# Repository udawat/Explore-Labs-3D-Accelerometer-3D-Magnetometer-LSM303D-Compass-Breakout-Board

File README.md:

# Explore Labs 3D Accelerometer + 3D Magnetometer LSM303D Compass Breakout Board
## Overview

[Explore Labs 3D Accelerometer + 3D Magnetometer LSM303D Compass Breakout Board](http://www.explorelabs.com/explore-labs-3d-accelerometer-3d-magnetometer-lsm303d-compass-breakout-board-5v-ready-with-voltage-regulator "Explore Labs 3D Accelerometer + 3D Magnetometer LSM303D Compass Breakout Board") is based on the ST LSM303D sensor, a 3D digital linear acceleration sensor and a 3D digital magnetic sensor that is ideal for making a tilt-compensated compass.

The LSM303D includes an I2C serial bus interface that supports standard and fast mode (100 kHz and 400 kHz) and SPI serial standard interface. The system can be configured to generate an interrupt signal for free-fall, motion detection and magnetic field detection. Thresholds and timing of interrupt generators are programmable by the end user. Magnetic and accelerometer blocks can be enabled or put into power-down mode separately.

The carrier board includes a low-dropout linear voltage regulator that provides the 3.3 V required by the LSM303D, which allows the sensor to be powered from 2.5 V to 5.5 V. The regulator output is available on the 3Vo pin which can supply approx. 150 mA to external devices.

The breakout board also includes a circuit that shifts the two I2C lines or all four SPI lines (clock, data-in/out and chip select) to the same logic voltage level as the supplied VIN, making it simple to interface the board with 5V systems; and the board’s 0.1″ pin spacing makes it easy to use with standard solderless breadboards and 0.1″ perfboards. The board ships fully populated with its SMD components, including the LSM303D, as shown in the product picture.

## Features of Explore Labs 3D Accelerometer + 3D Magnetometer LSM303D Compass Breakout Board:
* Wide supply voltage - 2.5V to 5V
* Level shifted IO lines for easy interfacing to high voltage boards like Arduino Uno, Mega, Leonardo, etc.
* All pins of the LSM303D sensor are available like I2C and SPI communication interfaces as well as INT1 and INT2 Interrupt pins
* Layout takes care of keeping the area below the sensor free from any active current carrying trace or a power or ground plane
* Capacitors with low ESR characteristics are used for decoupling on both VDD and VDDIO power inputs
* Open Source Hardware
* Designed, Assembled and Made in India

## Features of LSM303D Sensor IC:
* 3 magnetic field channels and 3 acceleration channels
* &plusmn;2/&plusmn;4/&plusmn;8/&plusmn;12 gauss magnetic full scale
* &plusmn;2/&plusmn;4/&plusmn;6/&plusmn;8/&plusmn;16 g linear acceleration full scale
* 16-bit data output
* SPI / I2C serial interfaces
* Power-down mode / low-power mode
* Extended operating temperature range (from -40 °C to 85 °C)
* Programmable interrupt generators for free-fall, motion detection and magnetic field detection
* Embedded temperature sensor
* Embedded FIFO

## Specifications:
* Input Voltage: 2.5V to 5V
* 5V Ready IOs: Level shifted IO lines for easy interfacing to incompatible voltage boards
* Digital Output: Inter Integrated Circuit (I2C/IIC) or Serial Peripheral Interface (SPI)
* Regulator Pin - Provides 3.3V Out at 150mA (when 3.6V < VIN < 5V) else provides voltage ~equal to VIN
* Dimensions: 20.4 mm x 20 mm
* Weight: 3 grams

## Applications:
* Tilt-compensated compasses
* Map rotation
* Position detection
* Motion-activated functions
* Free-fall detection
* Click/double-click recognition
* Pedometers
* Intelligent power saving for handheld devices
* Display orientation
* Gaming and virtual reality input devices
* Impact recognition and logging
* Vibration monitoring and compensation

## Output Format:
Values are expressed in 16-bits as two’s complement for each axis. As shown in the example codes below, knowing the sensitivites of the device, one can easily find out the acceleration value in g (acceleration due to gravity) and magnetic field intensity in gauss. These readings may be used separately or together to create a tilt-compensated compass or other complex orientation calculations for Inertial Measurement Units (IMU).

## Pinout Table for Explore Labs 3D Accelerometer + 3D Magnetometer LSM303D Compass Breakout
|Pin|5V Safe?   |Function|
|---|-----------|--------|
|VIN|Yes|**Input Voltage** Pin: 2.5V to 5.0V (depending on Master device being used as mentioned in later connection sections and tables below)|
|3Vo|Not Applicable|This is the output pin of the onboard 3.3V Voltage Regulator. It provides a clean and regulated 3.3V output to the sensor IC. It can also be used by the user to provide power to external devices or sensors. Maximum current that can be sourced easily would be approximately 125mA to 150mA after leaving some room for the on board sensor IC|
|GND|Not Applicable|Ground Connection. Connect this pin to the master device's ground pin or to any externally powered devices from onboard regulator|
|SDI/SDA|Yes. Bidirectional MOSFET with 4K7 pull-ups|This pin has dual functions - **Serial Data Input** (for SPI) or **Serial Data** (for I2C). In case of SPI, it can also be called as Master Out Slave In (MOSI)|
|SCK/SCL|Yes. Bidirectional MOSFET with 4K7 pull-ups|This pin is the **Serial Clock** input pin. It is common for both SPI and I2C interfaces|
|SDO/ADR|Yes. Only a 4K7 pull-up resistor needed as this is an output pin|This pin has dual functions - **Serial Data Output** (for SPI) or **Address Select** (for I2C). Also called as SA0. In case of SPI, it can also be called as Master In Slave Out (MOSI). In case of I2C, this pin may be pulled LOW or grounded for selecting an alternate address to avoid address conflicts with similar I2C devices. The change will have to be updated in code as well. Leave unconnected if no change in address required for I2C|
|CS|Yes. Bidirectional MOSFET with 4K7 pull-ups|**Chip Select** or Slave Select pin. By default, it is pulled HIGH using an onboard 4K7 pull-up resistor. This sets the default mode of communication for the sensor IC as I2C. For SPI, this pin acts as the chip select pin to communicate with an SPI master device. Leave unconnected when using I2C|
|INT1|No|Interrupt output pin. The LSM303D interrupt signal can be configured in a very flexible way allowing to recognize independent magnetic field detections of the X, Y and Z-axis. Or, independently recognize inertial events like an interrupt is generated when orientation moves from an unknown zone to a known zone. Single click and double clicks on any individual axis can easily be detected using any interrupt pin. FIFO Programmable threshold level, FIFO_empty or FIFO_Full events can be enabled to generate dedicated interrupts on the INT 1 or INT 2 pin. Also, An interrupt can be generated when the magnetic field value exceeds the user-defined threshold. The threshold and the timing of the two interrupt pins (INT 1 and INT 2) can be completely programmed by the user through the I2C/SPI interfaces. A detailed explanation is available in the ST LSM303D datasheet|
|INT2|No|Second Interrupt output pin. This pin acts as an additional interrupt pin for the LSM303D. It has the same functionality as of the INT1 pin. For more details, see INT1|
|GND|Not Applicable|Second Ground connection. Optionally, connect this pin to the master device's ground pin or to any externally powered devices from onboard regulator|

## Connections

The carrier board supports both I2C as well as SPI method of communication with a host microcontroller. The communication mode is selected by pulling the CS pin HIGH or LOW. By default, the CS pin is pulled HIGH through a 4.7 kΩ resistor on the board. This makes I2C communication the default method to talk to this carrier board.

**I2C Communication**: By default, I2C communication is implemented. The Explore Labs 3D Accelerometer + 3D Magnetometer LSM303D Compass Breakout Board can be configured and its angular velocity readings can be queried through the I2C bus. Level shifters on the I2C clock (SCL) and data (SDA) lines enable I2C communication with microcontrollers operating at the same voltage as VIN (2.5V to 5V). A detailed explanation of the I2C interface on the LSM303D can be found in its [datasheet][1] and more detailed information about I2C Protocol in general can be found in [NXP’s I2C-bus specification manual][2].

**I2C Address**: In I2C mode, the device’s 7-bit slave address has its least significant bit (LSb) determined by the voltage on the SDO/ADR pin. The carrier board pulls SDO/ADR HIGH through a 4.7 kΩ resistor, making the LSb 1 and setting the slave address to 0011101b (0x1D). This is the default device address in I2C mode. If SDO/ADR pin is connected to ground, LSb value is ‘0’ which changes the device address to 0011110b (0x1E). This solution permits the connection and addressing of two different accelerometers to the same I2C lines.

**Arduino Uno with I2C Interface**
* Sensor VIN - Arduino Uno 5V
* Sensor GND - Arduino Uno GND
* Sensor SDI/SDA - Arduino Uno Analog Input Pin A4 or SDA
* Sensor SCK/SCL - Arduino Uno Analog Input Pin A5 or SCL

**Raspberry Pi (all models) with I2C Interface**
* Sensor VIN - Raspberry Pi 3.3V on Pin 1 or 17
* Sensor GND - Raspberry Pi GND
* Sensor SDI/SDA - Raspberry Pi SDA1 (I2C) on Pin 3 or GPIO2
* Sensor SCK/SCL - Raspberry Pi SCL1 (I2C) on Pin 5 or GPIO3

**BeagleBone Black with I2C Interface**
* Sensor VIN - BeagleBone Black 3.3V
* Sensor GND - BeagleBone Black GND
* Sensor SDI/SDA - BeagleBone Black I2C2_SDA (Pin 20) on Header P9
* Sensor SCK/SCL - BeagleBone Black I2C2_SCL (Pin 19) on Header P9

## Connecting Explore Labs 3D Accelerometer + 3D Magnetometer LSM303D Compass Breakout Board using I2C (Inter Integrated Circuit) Interface
|L3GD20H|Arduino Uno|Arduino Mega|Arduino Leonardo|Arduino Due|Genuino Zero|Genuino 101|Arduino MKR1000|Raspberry Pi|BeagleBone Black|
|---|---|---|---|---|---|---|---|---|---|
|**VIN**|5V|5V|5V|3.3V|3.3V|VCC (3.3V)|3.3V|3.3V|3.3V|
|**GND**|GND|GND|GND|GND|GND|GND|GND|GND|GND|
|**SDI/SDA**|A4 or SDA|Pin 20 (SDA)|Pin 2 (SDA)|Pin 20 (SDA)|SDA|SDA|Pin 12 (SDA)|Pin 3 (SDA1) or GPIO2|Pin 20 (I2C2_SDA)|
|**SCK/SCL**|A5 or SCL|Pin 21 (SCL)|Pin 3 (SCL)|Pin 21 (SCL)|SCL|SCL|Pin 11 (SCL)|Pin 5 (SCL1) or GPIO3|Pin 19 (I2C2_SCL)|

## SPI Communication:
To use the LSM303D in SPI mode, CS pin must be driven low (connected to GND). A minimum of four logic connections are used viz., SDI, SCK, SDO and CS. These should be connected to an SPI bus operating at the same logic level as VIN. The SPI interface operates in 4-wire mode by default, with SDI and SDO on separate pins. In the default 4-wire mode, the sensor transmits data to the SPI master on a dedicated data out (SDO) line. If the SPI interface is configured to use 3-wire mode instead, the SDI line doubles as SDO and is driven by the LSM303D when it transmits data to the master. A detailed explanation of the SPI interface on the LSM303D can be found in its [datasheet][1].

**Arduino Uno with Serial Peripheral Interface (SPI)**
* Sensor VIN - Arduino Uno 5V
* Sensor GND - Arduino Uno GND
* Sensor SDI/SDA - Arduino Uno Digital Pin 11 or MOSI (Master Out Slave In)
* Sensor SCK/SCL - Arduino Uno Digital Pin 13 or SCK (Serial Clock)
* Sensor SDO/ADR - Arduino Uno Digital Pin 12 or MISO (Master In Slave Out)
* Sensor CS - Arduino Uno Digital Pin 10 or SS (Slave Select or Chip Select)

**Raspberry Pi (all models) with Serial Peripheral Interface (SPI)**
* Sensor VIN - Raspberry Pi 3.3V on Pin 1 or 17
* Sensor GND - Raspberry Pi GND
* Sensor SDI/SDA - Raspberry Pi `MOSI` (SPI) on Pin 19 or GPIO10
* Sensor SCK/SCL - Raspberry Pi `SCLK` (SPI) on Pin 23 or GPIO11
* Sensor SDO/ADR - Raspberry Pi `MISO` (SPI) on Pin 21 or GPIO9
* Sensor CS - Raspberry Pi `CE0_N` (SPI) on Pin 24 or GPIO8

**BeagleBone Black with Serial Peripheral Interface (SPI)**
* Sensor VIN - BeagleBone Black 3.3V
* Sensor GND - BeagleBone Black GND
* Sensor SDI/SDA - BeagleBone Black `SPI0_D0` (Pin 21) on Header P9
* Sensor SCK/SCL - BeagleBone Black `SPI0_SCLK` (Pin 22) on Header P9
* Sensor SDO/ADR - BeagleBone Black `SPI0_D1` (Pin 18) on Header P9
* Sensor CS - BeagleBone Black `SPI0_CS0` (Pin 17) on Header P9

## Connecting Explore Labs 3D Accelerometer + 3D Magnetometer LSM303D Compass Breakout Board using Serial Peripheral Interface (SPI)
|L3GD20H|Arduino Uno|Arduino Mega|Arduino Leonardo|Arduino Due|Genuino Zero|Genuino 101|Arduino MKR1000|Raspberry Pi|BeagleBone Black|
|---|---|---|---|---|---|---|---|---|---|
|**VIN**|5V|5V|5V|3.3V|3.3V|VCC (3.3V)|3.3V|3.3V|3.3V|
|**GND**|GND|GND|GND|GND|GND|GND|GND|GND|GND|
|**SDI/SDA**|Pin 11 or MOSI|Pin 51|Pin 4 (ICSP)|Pin 4 (ICSP)|Pin 4 (ICSP)|Pin 11 (MOSI)|Pin 8 (MOSI)|Pin 19 (`MOSI`) or GPIO10|Pin 21 (`SPI0_D0`)|
|**SCK/SCL**|Pin 13 or SCK|Pin 52|Pin 3 (ICSP)|Pin 3 (ICSP)|Pin 3 (ICSP)|Pin 13|Pin 9|Pin 23 (`SCLK`) or GPIO11|Pin 22 (`SPI0_SCLK`)|
|**SDO/ADR**|Pin 12 or MISO|Pin 50|Pin 1 (ICSP)|Pin 1 (ICSP)|Pin 1 (ICSP)|Pin 12 (MISO)|Pin 10 (MISO)|Pin 21 (`MISO`) or GPIO9|Pin 18 (`SPI0_D1`)|
|**CS**|Pin 10 or SS|Pin 53|Any IO|Any IO|Any IO|Pin 10|Any IO|Pin 24 (`CE0_N`) or GPIO8|Pin 17 (`SPI0_CS0`)|

## Resources:
[1]: www.st.com/resource/en/datasheet/lsm303d.pdf
[2]: http://www.nxp.com/documents/user_manual/UM10204.pdf
[Datasheet ST LSM303D: e-compass: 3D accelerometer and 3D magnetometer module](www.st.com/resource/en/datasheet/lsm303d.pdf "Datasheet ST LSM303D: e-compass: 3D accelerometer and 3D magnetometer module")

## Code:
Sample code is provided for interfacing the Explore Labs 3D Accelerometer + 3D Magnetometer LSM303D Compass Breakout Board to an Arduino Uno. After choosing the communication method (I2C or SPI), following code examples can be used to test the sensor.

**Using SPI**:
```c
/*
 * Interface Code for Explore Labs 3D Accelerometer + 3D Magnetometer
 * LSM303D Compass Breakout Board and Arduino Uno. This code assumes
 * selected communication method is Serial Peripheral Interface (SPI)
 * and hardware connections are made as follows:
 * 
 * Sensor VIN - Arduino Uno 5V or 3.3V
 * Sensor GND - Arduino Uno GND
 * Sensor SDI/SDA - Arduino Uno Digital Pin 11 or MOSI (Master Out Slave In)
 * Sensor SCK/SCL - Arduino Uno Digital Pin 13 or SCK (Serial Clock)
 * Sensor SDO/ADR - Arduino Uno Digital Pin 12 or MISO (Master In Slave Out)
 * Sensor CS - Arduino Uno Digital Pin 10 or SS (Slave Select or Chip Select)
 */
 
#include <SPI.h>          // Include Arduino SPI library

#define OUT_X_L_M   0x08  // Register addresses from sensor datasheet.
#define OUT_X_H_M   0x09  // Only the registers that are used
#define OUT_Y_L_M   0x0A  // in this program are defined here.
#define OUT_Y_H_M   0x0B
#define OUT_Z_L_M   0x0C
#define OUT_Z_H_M   0x0D
#define CTRL1       0x20
#define CTRL5       0x24
#define CTRL7       0x26
#define OUT_X_L_A   0x28
#define OUT_X_H_A   0x29
#define OUT_Y_L_A   0x2A
#define OUT_Y_H_A   0x2B
#define OUT_Z_L_A   0x2C
#define OUT_Z_H_A   0x2D

int8_t readData   = 0x80;
int8_t writeData  = 0x00;

int16_t ax, ay, az;       // 16-bit variables to hold raw data from sensor
int16_t mx, my, mz;
float heading;

const int CS = 10;        // Chip Select pin for SPI

void setup() {
  Serial.begin(9600);
  SPI.begin();
  pinMode(CS, OUTPUT);
  writeReg(CTRL1, 0x37);  // Initialize the sensor by setting
  writeReg(CTRL5, 0x04);  // control registers
  writeReg(CTRL7, 0x00);  
  delay(100);
}

void loop() {  
  mx = (int16_t) readReg(OUT_X_H_M) <<8 | readReg(OUT_X_L_M); // typecast as
  my = (int16_t) readReg(OUT_Y_H_M) <<8 | readReg(OUT_Y_L_M); // 16-bit
  mz = (int16_t) readReg(OUT_Z_H_M) <<8 | readReg(OUT_Z_L_M);
  ax = (int16_t) readReg(OUT_X_H_A) <<8 | readReg(OUT_X_L_A);
  ay = (int16_t) readReg(OUT_Y_H_A) <<8 | readReg(OUT_Y_L_A);
  az = (int16_t) readReg(OUT_Z_H_A) <<8 | readReg(OUT_Z_L_A);
  
  Serial.print("Magnetic Field (Gauss):\t");
  
  //Sensitivity from Page 10 of datasheet - use 0.08 mili-gauss/LSB for default +-2gauss.
  Serial.print(mx*0.00008F, DEC); Serial.print("\t");
  Serial.print(my*0.00008F, DEC); Serial.print("\t");
  Serial.print(mz*0.00008F, DEC); Serial.print("\t");
  Serial.println();

  Serial.print("Acceleration due to gravity (g):\t");
  
  //Sensitivity from Page 10 of datasheet - use 0.061 mili-g/LSB for default +-2g.
  Serial.print("X-Axis_A: ");
  Serial.print(ax*0.000061F, DEC); Serial.print("\t");
  Serial.print(ay*0.000061F, DEC); Serial.print("\t");
  Serial.print(az*0.000061F, DEC); Serial.print("\t");
  Serial.println();

  heading = atan2(my, mx);// Calculation for heading. North is zero degrees.
  if(heading < 0)
    heading += 2 * M_PI;
  Serial.println(heading * 180/M_PI);
  
  delay(100);
}

int8_t readReg(int8_t address) {
  int8_t buffer = 0;
  digitalWrite(CS, LOW); 
  SPI.transfer(readData | address);
  buffer = SPI.transfer(writeData);
  digitalWrite(CS, HIGH);
  return(buffer);  
}

void writeReg(int8_t address, int8_t val) {
  digitalWrite(CS, LOW);
  SPI.transfer(writeData | address);
  SPI.transfer(val);
  digitalWrite(CS, HIGH);
}
```

**Using I2C**:
```c
/*
 * Interface Code for Explore Labs 3D Accelerometer + 3D Magnetometer
 * LSM303D Compass Breakout Board and Arduino Uno. This code assumes
 * selected communication method is Inter Integrated Circuit (I2C)
 * Interface and hardware connections are made as follows:
 * 
 * Sensor VIN - Arduino Uno 5V or 3.3V
 * Sensor GND - Arduino Uno GND
 * Sensor SDI/SDA - Arduino Uno Analog Input Pin A4
 * Sensor SCK/SCL - Arduino Uno Analog Input Pin A5 
 */
 
#include <Wire.h>         // Include Arduino I2C library

#define OUT_X_L_M   0x08  // Register addresses from sensor datasheet.
#define OUT_X_H_M   0x09  // Only the registers that are used
#define OUT_Y_L_M   0x0A  // in this program are defined here.
#define OUT_Y_H_M   0x0B
#define OUT_Z_L_M   0x0C
#define OUT_Z_H_M   0x0D
#define CTRL1       0x20
#define CTRL5       0x24
#define CTRL7       0x26
#define OUT_X_L_A   0x28
#define OUT_X_H_A   0x29
#define OUT_Y_L_A   0x2A
#define OUT_Y_H_A   0x2B
#define OUT_Z_L_A   0x2C
#define OUT_Z_H_A   0x2D

int8_t readData   = 0x01;
int8_t writeData  = 0x00;
int8_t address    = 0x1D; // Device address of LSM303D with SDO/ADR/SA0 pulled HIGH.
//int8_t address  = 0x1E; // Device address of LSM303D with SDO/ADR/SA0 connected to GND.

int16_t ax, ay, az;       // 16-bit variables to hold raw data from sensor
int16_t mx, my, mz;
float heading;

void setup() {
  Serial.begin(9600);
  Wire.begin();
  writeReg(CTRL1, 0x37);  // Initialize the sensor by setting
  writeReg(CTRL5, 0x08);  // control registers
  writeReg(CTRL7, 0x00);  
  delay(100);
}

void loop() {  
  mx = (int16_t) readReg(OUT_X_H_M) <<8 | readReg(OUT_X_L_M); // typecast as
  my = (int16_t) readReg(OUT_Y_H_M) <<8 | readReg(OUT_Y_L_M); // 16-bit
  mz = (int16_t) readReg(OUT_Z_H_M) <<8 | readReg(OUT_Z_L_M);
  ax = (int16_t) readReg(OUT_X_H_A) <<8 | readReg(OUT_X_L_A);
  ay = (int16_t) readReg(OUT_Y_H_A) <<8 | readReg(OUT_Y_L_A);
  az = (int16_t) readReg(OUT_Z_H_A) <<8 | readReg(OUT_Z_L_A);
  
  Serial.print("Magnetic Field (Gauss):\t");
  
  //Sensitivity from Page 10 of datasheet - use 0.08 mili-gauss/LSB for default +-2gauss.
  Serial.print(mx*0.00008F, DEC); Serial.print("\t");
  Serial.print(my*0.00008F, DEC); Serial.print("\t");
  Serial.print(mz*0.00008F, DEC); Serial.print("\t");
  Serial.println();

  Serial.print("Acceleration due to gravity (g):\t");
  
  //Sensitivity from Page 10 of datasheet - use 0.061 mili-g/LSB for default +-2g.
  Serial.print("X-Axis_A: ");
  Serial.print(ax*0.000061F, DEC); Serial.print("\t");
  Serial.print(ay*0.000061F, DEC); Serial.print("\t");
  Serial.print(az*0.000061F, DEC); Serial.print("\t");
  Serial.println();

  heading = atan2(my, mx);// Calculation for heading. North is zero degrees.
  if(heading < 0)
    heading += 2 * M_PI;
  Serial.println(heading * 180/M_PI);
  
  delay(100);
}

int8_t readReg(int8_t reg){
  int8_t buffer = 0;
  Wire.beginTransmission((address | writeData) >>1);
  Wire.write(reg);
  Wire.endTransmission(0);
  Wire.requestFrom((address | readData) >>1 , 1);
  while( Wire.available() == 0);
  buffer = Wire.read();
  Wire.endTransmission();
  return(buffer);  
}

void writeReg(int8_t reg, int8_t val) {
  Wire.beginTransmission((address | writeData) >>1);
  Wire.write(reg);
  Wire.write(val);
  Wire.endTransmission();
}
```

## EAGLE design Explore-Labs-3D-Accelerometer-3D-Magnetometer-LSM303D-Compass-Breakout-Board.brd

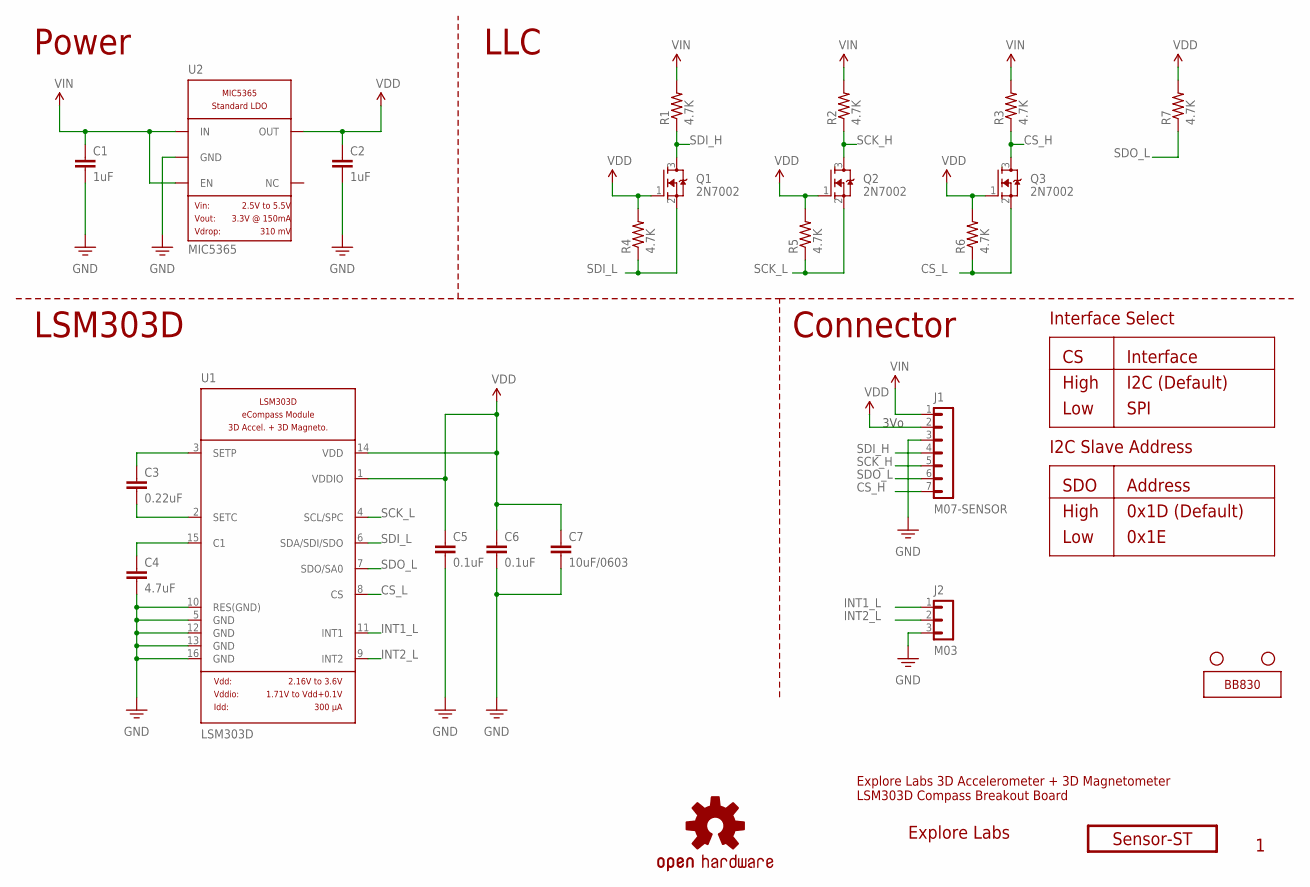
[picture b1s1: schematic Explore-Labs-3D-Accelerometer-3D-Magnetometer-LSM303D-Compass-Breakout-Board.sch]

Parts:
C1, C2: 1uF; 0402-CAP
C3: 0.22uF; 0402-CAP
C4: 4.7uF; 0402-CAP
C5, C6: 0.1uF; 0402-CAP
C7: 10uF/0603; 0603-CAP
H1, H2: STAND-OFF
J1: M07-SENSOR; 1X07-SENSOR-SPI
J2: M03; 1X03
Q1, Q2, Q3: 2N7002; SOT23
R1, R2, R3, R4, R5, R6, R7: 4.7K; 0402-RES
U1: LSM303D; LGA16-LSM303D
U2: MIC5365; SOT23-LDO
ZZ1: EXPLORE-LABS-LOGO-2-0.25; EXLABS_LOGO_0.25
ZZ2: OSHW-LOGOBOTTOM; OSHW-LOGO-M-BOTTOM
ZZ3: SENSOR-ST
ZZ4: BREADBOARD-830

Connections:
CS_H: J1.7, Q3.3 (D), R3.1
CS_L: Q3.2 (S), R6.1, U1.8 (CS)
GND: C1.2, C2.2, C4.2, C5.2, C6.2, C7.2, J1.3, J2.3, U1.5 (GND), U1.10 (RES(GND)), U1.12 (GND), U1.13 (GND), U1.16 (GND), U2.2 (GND)
INT1_L: J2.1, U1.11 (INT1)
INT2_L: J2.2, U1.9 (INT2)
unnamed: C4.1, U1.15 (C1)
unnamed: C3.2, U1.2 (SETC)
unnamed: C3.1, U1.3 (SETP)
SCK_H: J1.5, Q2.3 (D), R2.1
SCK_L: Q2.2 (S), R5.1, U1.4 (SCL/SPC)
SDI_H: J1.4, Q1.3 (D), R1.1
SDI_L: Q1.2 (S), R4.1, U1.6 (SDA/SDI/SDO)
SDO_L: J1.6, R7.1, U1.7 (SDO/SA0)
VDD: C2.1, C5.1, C6.1, C7.1, J1.2, Q1.1 (G), Q2.1 (G), Q3.1 (G), R4.2, R5.2, R6.2, R7.2, U1.1 (VDDIO), U1.14 (VDD), U2.5 (OUT)
VIN: C1.1, J1.1, R1.2, R2.2, R3.2, U2.1 (IN), U2.3 (EN)

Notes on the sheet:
LLC
Power
3Vo
Connector
I2C (Default)
SPI
High
Low
Interface
0x1D (Default)
0x1E
Address
SDO
Interface Select
I2C Slave Address
LSM303D
Explore Labs 3D Accelerometer + 3D Magnetometer LSM303D Compass Breakout Board

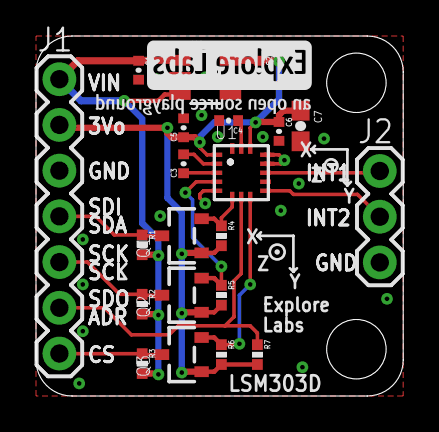
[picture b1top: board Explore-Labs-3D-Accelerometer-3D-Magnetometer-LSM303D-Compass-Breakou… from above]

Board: 2 copper layers, 20.4 x 20.0 mm, 27 parts (1 on the bottom side), 15 nets.

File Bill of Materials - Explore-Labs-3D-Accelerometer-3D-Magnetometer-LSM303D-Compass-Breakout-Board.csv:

"Qty";"Value";"Device";"Package";"Parts";"Description";"";
"2";"0.1uF";"CAPACITOR-0402";"0402-CAP";"C5, C6";"";"";
"1";"0.22uF";"CAPACITOR-0402";"0402-CAP";"C3";"";"";
"1";"10uF/0603";"CAPACITOR-0603";"0603-CAP";"C7";"";"";
"2";"1uF";"CAPACITOR-0402";"0402-CAP";"C1, C2";"";"";
"3";"2N7002";"MOSFET-N-2N7002P";"SOT23";"Q1, Q2, Q3";"2N7002P";"";
"7";"4.7K";"RESISTOR-0402";"0402-RES";"R1, R2, R3, R4, R5, R6, R7";"";"";
"1";"4.7uF";"CAPACITOR-0402";"0402-CAP";"C4";"";"";
"1";"BREADBOARD-830";"BREADBOARD-830";"BREADBOARD-830";"ZZ4";"";"";
"1";"EXPLORE-LABS-LOGO-2-0.25";"EXPLORE-LABS-LOGO-2-0.25";"EXLABS_LOGO_0.25";"ZZ1";"Explore Labs Logo";"";
"1";"LSM303D";"LSM303D";"LGA16-LSM303D";"U1";"LSM303D";"";
"1";"M03";"M03";"1X03";"J2";"";"";
"1";"M07-SENSOR";"M07-SENSOR";"1X07-SENSOR-SPI";"J1";"Header 7";"";
"1";"MIC5365";"MIC5365";"SOT23-LDO";"U2";"";"";
"1";"OSHW-LOGOBOTTOM";"OSHW-LOGOBOTTOM";"OSHW-LOGO-M-BOTTOM";"ZZ2";"Open Source Hardware Logo";"";
"1";"SENSOR-ST";"SENSOR-ST";"SENSOR-ST";"ZZ3";"";"";
"2";"STAND-OFF";"STAND-OFF";"STAND-OFF";"H1, H2";"#4 Stand Off";"";

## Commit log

2016-06-22 initial commit
    added schematic in pdf, png and eagle format; board file and BOM
2016-06-22 added arduino code
2016-06-22 edits
2016-06-22 minor edits
2016-06-22 updated product images

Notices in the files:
parts and their libraries:
Explore Labs EAGLE Library: Released under the Creative Commons
Explore Labs EAGLE Library: http://creativecommons.org/licenses/by-sa/4.0
SparkFun-Aesthetics: Licensing: Creative Commons ShareAlike 4.0 International - https://creativecommons.org/licenses/by-sa/4.0
